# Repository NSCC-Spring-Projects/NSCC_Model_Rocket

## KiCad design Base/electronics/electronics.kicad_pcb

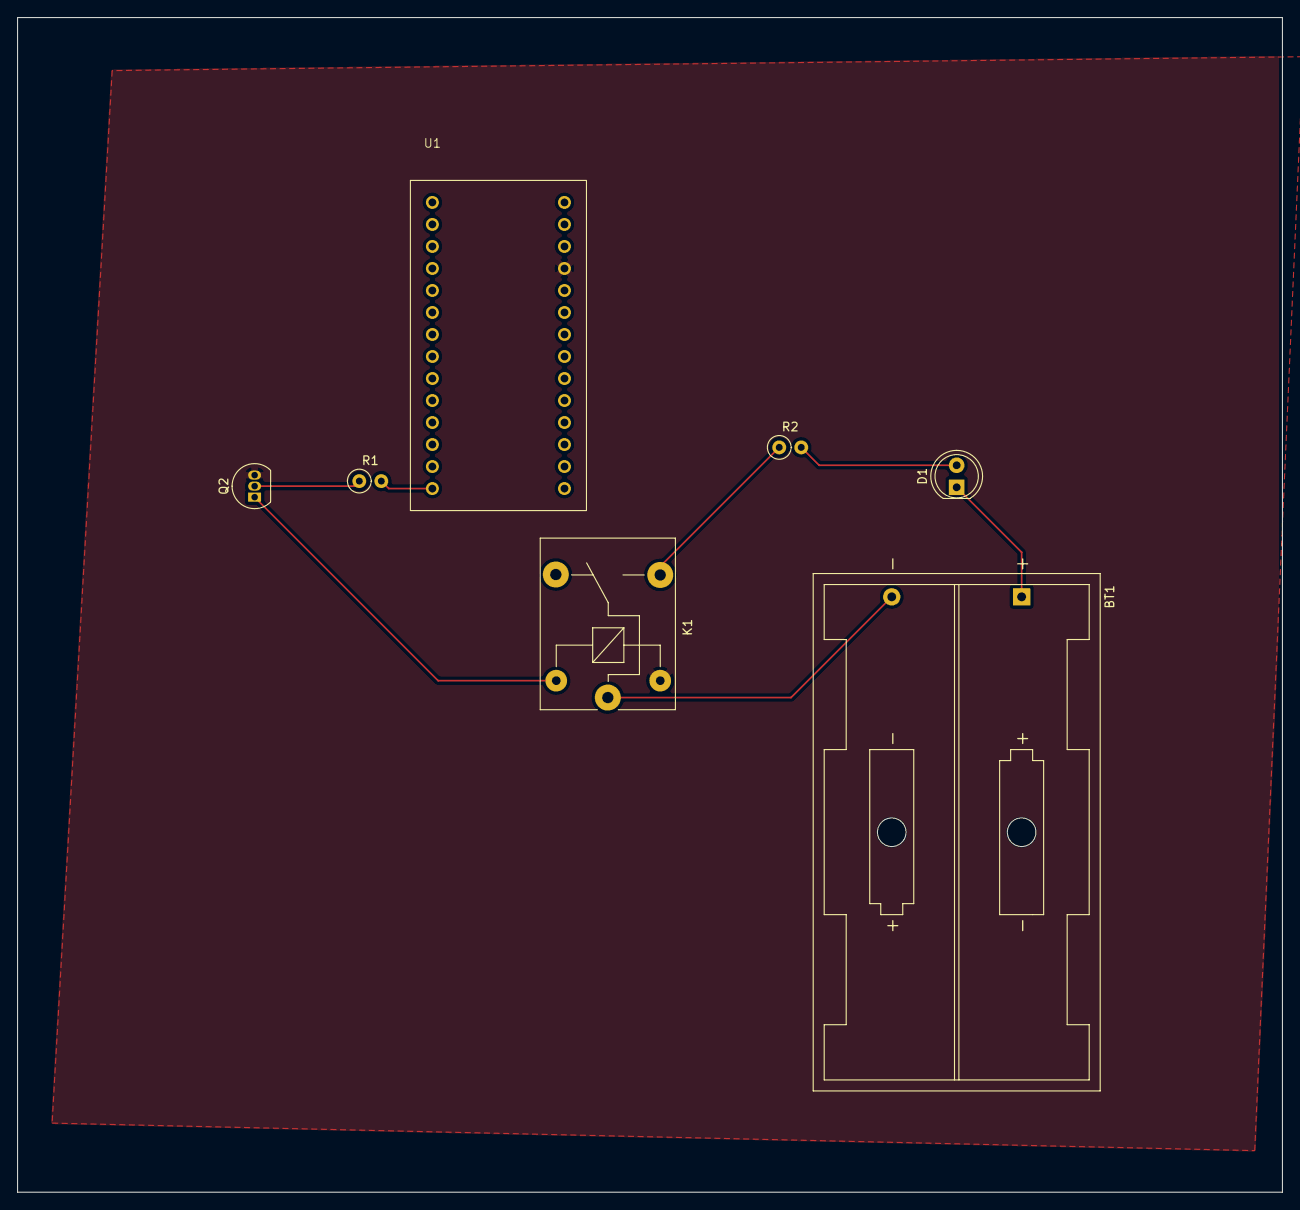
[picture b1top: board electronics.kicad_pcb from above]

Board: 2 copper layers, 146.0 x 135.6 mm, 7 parts (0 on the bottom side), 8 nets.

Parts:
BT1: 12v; BatteryHolder_Keystone_2462_2xAA
D1: LED; LED_D5.0mm
K1: SANYOU_SRD_Form_C; Relay_SPDT_SANYOU_SRD_Series_Form_C
Q2: BC547; TO-92_Inline
R1, R2: 1k; R_Axial_DIN0207_L6.3mm_D2.5mm_P2.54mm_Vertical
U1: MKR 1300

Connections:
GND: K1.2, Q2.3 (E), U1.18 (GND)
unnamed: BT1.1 (+), D1.1 (K)
unnamed: BT1.2 (-), K1.1
unnamed: D1.2 (A), R2.2
unnamed: K1.3, R2.1
unnamed: Q2.2 (B), R1.1
unnamed: K1.5, Q2.1 (C)
unnamed: R1.2, U1.14 (D5)

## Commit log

2026-04-28 add folder for new code
2026-04-30 schematic for new base wiring
2026-05-01 Scripts for calculating rocket data
2026-05-22 update schematic
2026-05-22 add readme for calculators
